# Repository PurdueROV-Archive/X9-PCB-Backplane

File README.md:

# X9-PCB-Backplane
This PCB will be used to interface with all the peripherals coming into and out of the main electronics tube.  This board will then connect to a shield which will have all of the electronic components attached to it.

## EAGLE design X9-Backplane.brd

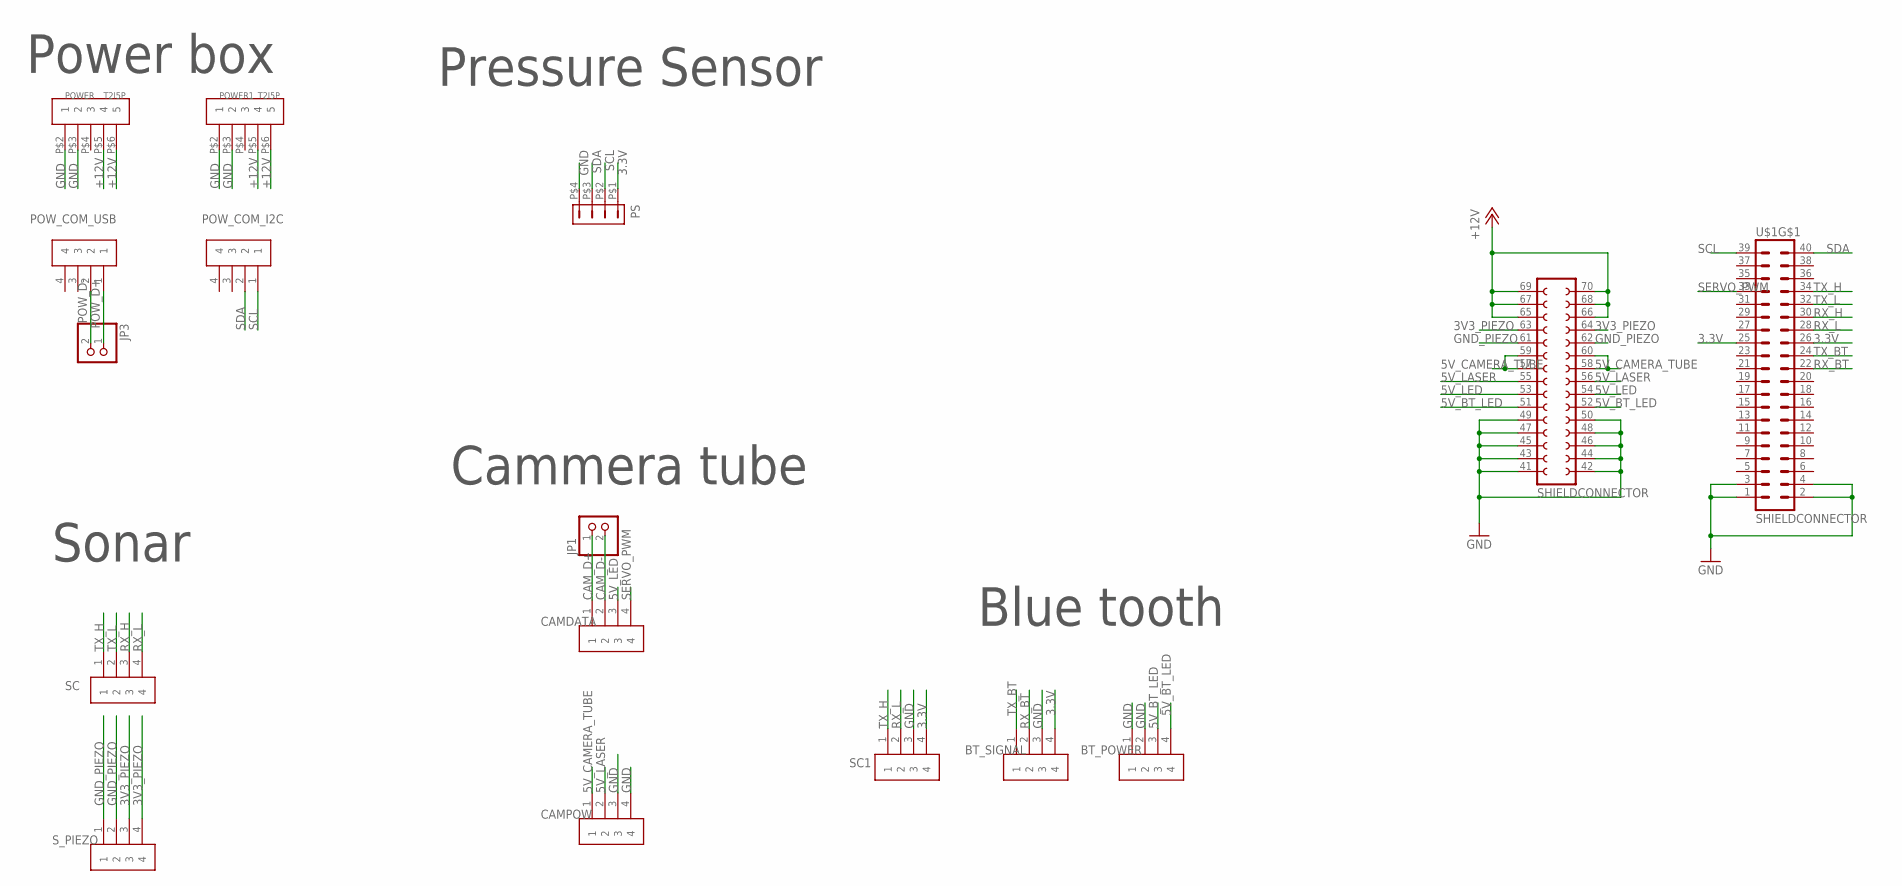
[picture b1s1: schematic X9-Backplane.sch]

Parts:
BT_POWER: T2I
BT_SIGNAL: T2I
CAMDATA: T2I
CAMPOW: T2I
JP1, JP3: PINHD-1X2; 1X02
POWER, POWER1: T2I5P
POW_COM_I2C: T2I
POW_COM_USB: T2I
PS: DF13-4P-1.25DSA
SC, SC1: T2I
S_PIEZO: T2I
U$1: SHIELDCONNECTOR; 20X2PIN

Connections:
3.3V: BT_SIGNAL.4, PS.P$1 (1), SC1.4, U$1.25, U$1.26
3V3_PIEZO: S_PIEZO.3, S_PIEZO.4, U$1.63 (3V3_PIEZO), U$1.64 (3V3_PIEZO)
5V_BT_LED: BT_POWER.3, BT_POWER.4, U$1.51 (5V_BT_LED), U$1.52 (5V_BT_LED)
5V_CAMERA_TUBE: CAMPOW.1, U$1.57 (5V_CAMERA_TUBE), U$1.58 (5V_CAMERA_TUBE), U$1.59 (19), U$1.60 (20)
5V_LASER: CAMPOW.2, U$1.55 (5V_LASER), U$1.56 (5V_LASER)
5V_LED: CAMDATA.3, U$1.53 (5V_LED), U$1.54 (5V_LED)
+12V: POWER.P$5 (4), POWER.P$6 (5), POWER1.P$5 (4), POWER1.P$6 (5), U$1.65 (12V), U$1.66 (12V), U$1.67 (12V), U$1.68 (12V), U$1.69 (12V), U$1.70 (12V)
CAM_D+: CAMDATA.1, JP1.1
CAM_D-: CAMDATA.2, JP1.2
GND: BT_POWER.1, BT_POWER.2, BT_SIGNAL.3, CAMPOW.3, CAMPOW.4, POWER.P$2 (1), POWER.P$3 (2), POWER1.P$2 (1), POWER1.P$3 (2), PS.P$4 (4), SC1.3, U$1.1, U$1.2, U$1.3, U$1.4, U$1.41 (GND), U$1.42 (GND), U$1.43 (GND), U$1.44 (GND), U$1.45 (GND), U$1.46 (GND), U$1.47 (GND), U$1.48 (GND), U$1.49 (GND), U$1.50 (GND)
GND_PIEZO: S_PIEZO.1, S_PIEZO.2, U$1.61 (GND_PIEZO), U$1.62 (GND_PIEZO)
POW_D+: JP3.1, POW_COM_USB.1
POW_D-: JP3.2, POW_COM_USB.2
RX_BT: BT_SIGNAL.2, U$1.22
RX_H: SC.3, U$1.30 (Z)
RX_L: SC.4, SC1.2, U$1.28 (Y)
SCL: POW_COM_I2C.1, PS.P$2 (2), U$1.39 (SCL)
SDA: POW_COM_I2C.2, PS.P$3 (3), U$1.40 (SDA)
SERVO_PWM: CAMDATA.4, U$1.33 (SERVO_PWM)
TX_BT: BT_SIGNAL.1, U$1.24
TX_H: SC.1, SC1.1, U$1.34 (A)
TX_L: SC.2, U$1.32 (B)

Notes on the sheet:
Blue tooth
Cammera tube
Power box
Pressure Sensor
Sonar

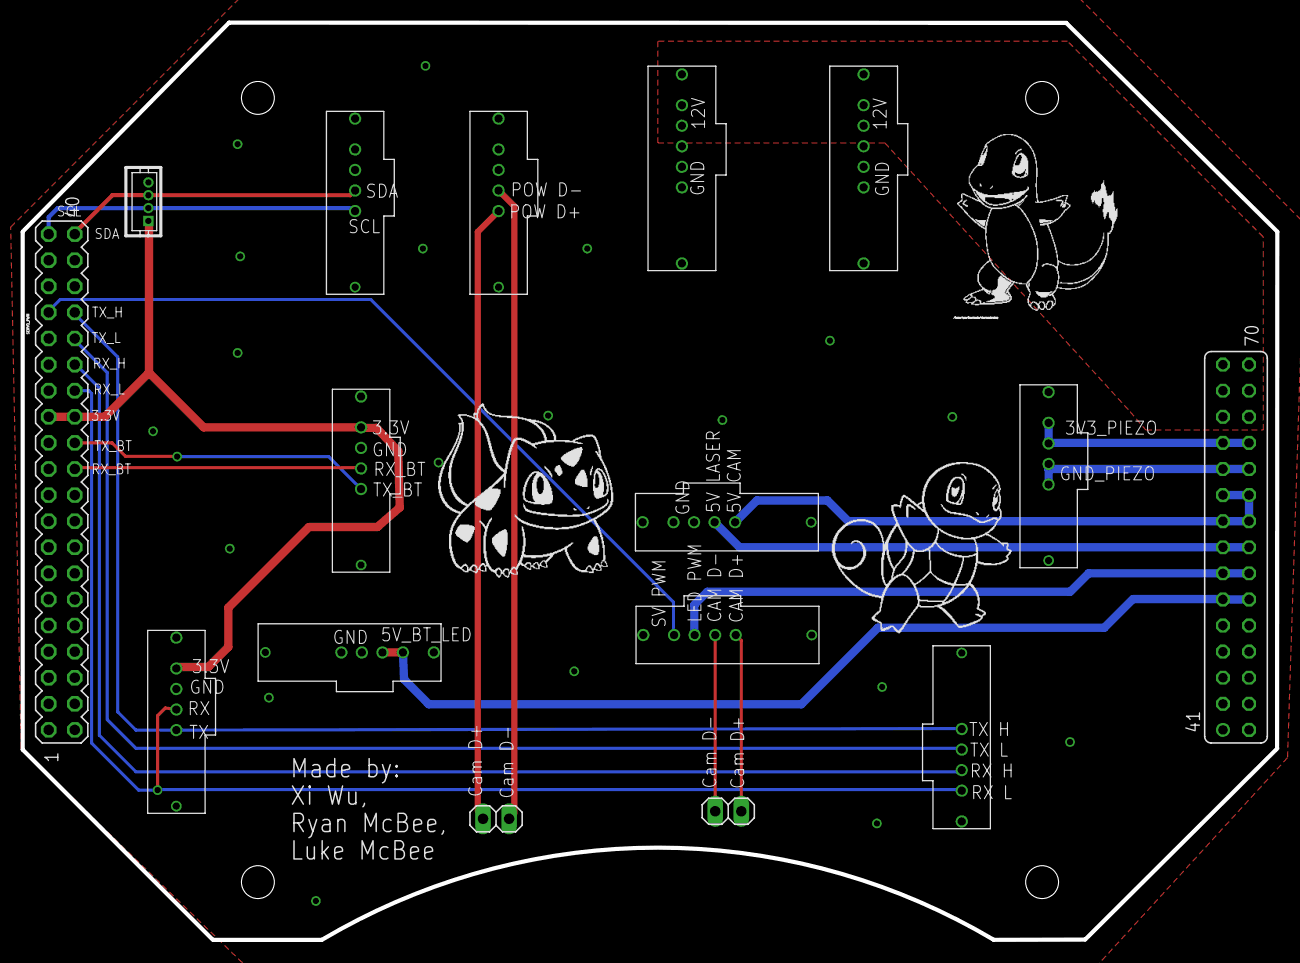
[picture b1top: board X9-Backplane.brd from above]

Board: 2 copper layers, 122.1 x 89.3 mm, 15 parts (0 on the bottom side), 22 nets.

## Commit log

2016-11-02 OutputJob
2016-11-05 added connectors
2016-12-04 created the backplane
2016-12-04 resizing the board
2016-12-04 modified 5V_BT_LED on board layout
2016-12-07 Modified BT and PS
2016-12-09 making backplane smaller
2016-12-10 rearanging physical layout
2016-12-10 add silkscreen
2016-12-18 added debugging pins
2016-12-22 Fixed routing issue
2016-12-23 added names
2016-12-24 reordered where the binders will be placed
2016-12-24 Moved around connector placement
2016-12-24 Added extra connector for bluetooth just in case
2016-12-24 minor edits to i2c
2016-12-26 added a lot of silk screen
2016-12-28 fixed labeling in schematic
2016-12-29 silk screen and wiring
2016-12-30 Edited the silkscreen
